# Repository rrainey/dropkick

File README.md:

# Dropkick
**An experimental logger for skydivers**

These devices are designed to be carried in a skydiver's breast pocket. The device loggs GPS position, barometric altitude, body rotation rates, and acceleration forces.
Data is logged to a SD card for analysis on the ground.

There are two board variants active in this project: V4 SAM, is the board I use for skydiving. V5-CAM is a design repurposed for real-time
use on a telescope pointing experiments. See [CHANGELOG.md](CHANGELOG.md) for a more detailed history.

## Sponsorship
I'd like to thank [PCBWay](https://www.pcbway.com/) for their generous sponsorship. PCBWay supplied prototype PCBs and solder stencils for the CAM variant of this project. My experience with PCBWay predates their sponsorship here. PCBWay has been a great choice for my projects. They deliver good PCBs and accurate stencils quickly.
 
 ## Description

This is a stand-alone, battery-powered data logger designed to be
carried by a skydiver during their jump.  It includes a GNSS (GPS) receiver, 6-DOF IMU, and altitude sensors. Data from all sensors is logged onto a Micro-SD card. The logged data can be reviewed post-jump by to-be-designed software.

One objective of this project is to research compact GNSS receiver performance in the dynamic environment that a skydiver routinely experiences. As such, there are currently two different u-blox receiver modules that I'm testing. There is a distinct PCB for each board variant.

## Directory Structure
* **pcb-sam** - KiCad 6 PCB project files for the [u-blox SAM-M10Q](https://content.u-blox.com/sites/default/files/SAM-M8Q_DataSheet_%28UBX-16012619%29.pdf) variant (this is the preferred variant for skydiving)
* **pcb-cam** - KiCad 7 PCB project files for the [u-blox CAM-M8](https://content.u-blox.com/sites/default/files/CAM-M8-FW3_DataSheet_%28UBX-15031574%29.pdf) variant
* **enclosure** - Fusion 360 enclosure; designed to be 3D-printed
* **firmware** - Arduino-based firmware for the microcontroller
* **images** - supporting images and videos
* **analysis** - GNU Octave-based log file analysis software

Gerber production files generated by KiCad are included in the PCB directories.

Exploded enclosure view (click to view)

## Specifications

Enclosure Dimensions: 58mm x 51mm x 20mm

Power: rechargeable 500mAh Li-Polymer battery

Unit Weight: 55 grams

Storage: removable microSD card

Log file format: [one log file for each jump](LOG-FORMAT.md); raw log format is an extension of NMEA0183.

USB micro-B connector (for recharging and programming)

Bootloader programmed via a 10-pin J-Link compatible connector; routine Arduino programming via the USB connector.

** Compiling Firmware
The Arduino board type should be set to "Adafruit Trinket M0" with Tiny USB enabled.

These libraries are required:
- Adafruit_BMP3XX
- ICM42688
- SparkFun u-blox GNSS Arduino_Library
- MicroNMEA  (2.0.6)
- SD (install the custom fork that I maintain on github)

## PCB Notes
My prototype circuit boards were fabricated by both OSHPark and PCBgogo. Both are excellent manufacturers for hobbyists.

### Bootloader

I flash all variants with the [Adafruit Trinket M0 UF2 bootloader](https://github.com/adafruit/uf2-samdx1/releases/download/v3.15.0/bootloader-trinket_m0-v3.15.0.bin) bin image. The current version is 3.15. Programming is performed via a Segger J-Link USB adapter using Microchip Studio (formerly Atmel Studio). Use Device = "ATSAMD21G18A". Program from the bootload .bin image file and then set the USER_WORD_0.NVMCTRL_BOOTPROT fuse to 8192 bytes.

## Solder Reflow

The solder reflow process has turned out to be a tricky step in constructing the PCBs, particularly with the SAM-M8Q IC.  Basically it requires extra heat soak in
  order to properly flow the solder.  Some u-blox instructions are repeated below, but I'll ultimately add some notes about what worked best for me.

The [u-blox Hardware Integration Manual](https://www.u-blox.com/en/docs/UBX-16018358) provides some detailed requirements for soldering the GNSS module to a PCB:

> ### Soldering paste

>Use of "no clean" soldering paste is highly recommended, as it does not require cleaning after the soldering process has taken place. The paste in the example below meets these criteria.

> * Soldering paste: OM338 SAC405 / Nr.143714 (Cookson Electronics)

> * Alloy specification: Sn 95.5/ Ag 4/ Cu 0.5 (95.5% tin/ 4% silver/ 0.5% copper)

> * Melting temperature: 217 °C

> * Stencil thickness: 120 um

> The final choice of the soldering paste depends on the approved manufacturing procedures. The paste-mask geometry for applying soldering paste should meet the recommendations. 

> ### Reflow soldering

> A convection-type soldering oven is highly recommended over the infrared-type radiation oven. Convection-heated ovens allow precise control of the temperature, and all parts will heat up evenly, regardless of material properties, thickness of components and surface color. As a reference, see the "IPC-7530 Guidelines for temperature profiling for mass soldering (reflow and wave) processes”, published in 2001.

> ### Preheat phase

>During the initial heating of component leads and balls, residual humidity will be dried out. Note that this preheat phase will not replace prior baking procedures.

> * Temperature rise rate: max. 3 °C/s. If the temperature rise is too rapid in the preheat phase it may cause excessive slumping.

> * Time: 60 - 120 s. If the preheat is insufficient, rather large solder balls tend to generate. Conversely, if performed excessively, fine balls and large balls will be generated in clusters.

> * End temperature: 150 - 200 °C. If the temperature is too low, non-melting tends to be caused in areas containing large heat capacity. 

> ### Heating and Reflow Phase

> The temperature rises above the liquidus temperature of 217 °C. Avoid a sudden rise in temperature as the slump of the paste could become worse.

> * Limit time above 217 °C liquidus temperature: 40 - 60s

> * Peak reflow temperature: 245 °C

SAC405 solder paste is relatively expensive. I have been unable to locate SAC405 in hobbyist-friendly quantities, so I opted to use SAC305 for these prototypes. The melting qualities are quite similar, and it retains the essential "no clean" properties required by U-blox -- at the cost of [potentially having slightly less sound solder connections](https://citeseerx.ist.psu.edu/viewdoc/download?doi=10.1.1.517.4830&rep=rep1&type=pdf#:~:text=The%20North%20American%20industry%20generally,comparable%20to%20that%20of%20SAC405.).

I own a very basic infrared-type reflow oven, a Puhui T962. Even though infrared ovens are not recommended by U-blox, I decided to use it and pay careful attention to the programming of heating profile. First, I did a series to timing experiments with the standard profiles comparing them against the u-blox requirements. It turned out that my oven does not have a standard heating profile that would comply with these requirements. In particular, the closest standard profile held the oven temperature above 217 °C for roughly 90 seconds. That's far longer than the 40 to 60 seconds stated in the requirements. I had to develop a custom profile to match.

I programmed this profile into the reflow oven:

## Enclosure Notes
The enclosure is designed to be 3D printed. Tolerances between the upper enclosure, lower enclosure, and the PCB
 are quite tight - printing precision will be important. Since 3D printing technologies will vary in their precision, 
 you may need to scale or otherwise modify the objects to adequately match the final measurements in the original design.

For example, I printed the prototype enclosure on a MakerBot Replicator 2 (PLA) printer.  Using the default print settings
 I know that an object will shrink typically by about 1% post-printing.  I set the scale to 101% to compensate for that 
 in the MakerBot Desktop tooling and the end result works well.

## Credits

This PCB design is based on several Adafruit Feather and Stemma QT sensor boards.  Adafruit maintains a family of
 excellent microcontroller and sensor evaluation boards and companion software.  Support them. They deserve it.

The enclosure for this project was designed using the personal edition of Fusion 360. Autodesk supports the Maker community through access to this epic design tool.  Try it out.

## Disclaimer
THE SOFTWARE IS PROVIDED "AS IS", WITHOUT WARRANTY OF ANY KIND, EXPRESS OR IMPLIED, INCLUDING BUT NOT LIMITED TO THE WARRANTIES OF MERCHANTABILITY,
FITNESS FOR A PARTICULAR PURPOSE AND NONINFRINGEMENT. IN NO EVENT SHALL THE
AUTHORS OR COPYRIGHT HOLDERS BE LIABLE FOR ANY CLAIM, DAMAGES OR OTHER
LIABILITY, WHETHER IN AN ACTION OF CONTRACT, TORT OR OTHERWISE, ARISING FROM,
OUT OF OR IN CONNECTION WITH THE SOFTWARE OR THE USE OR OTHER DEALINGS IN THE
SOFTWARE.

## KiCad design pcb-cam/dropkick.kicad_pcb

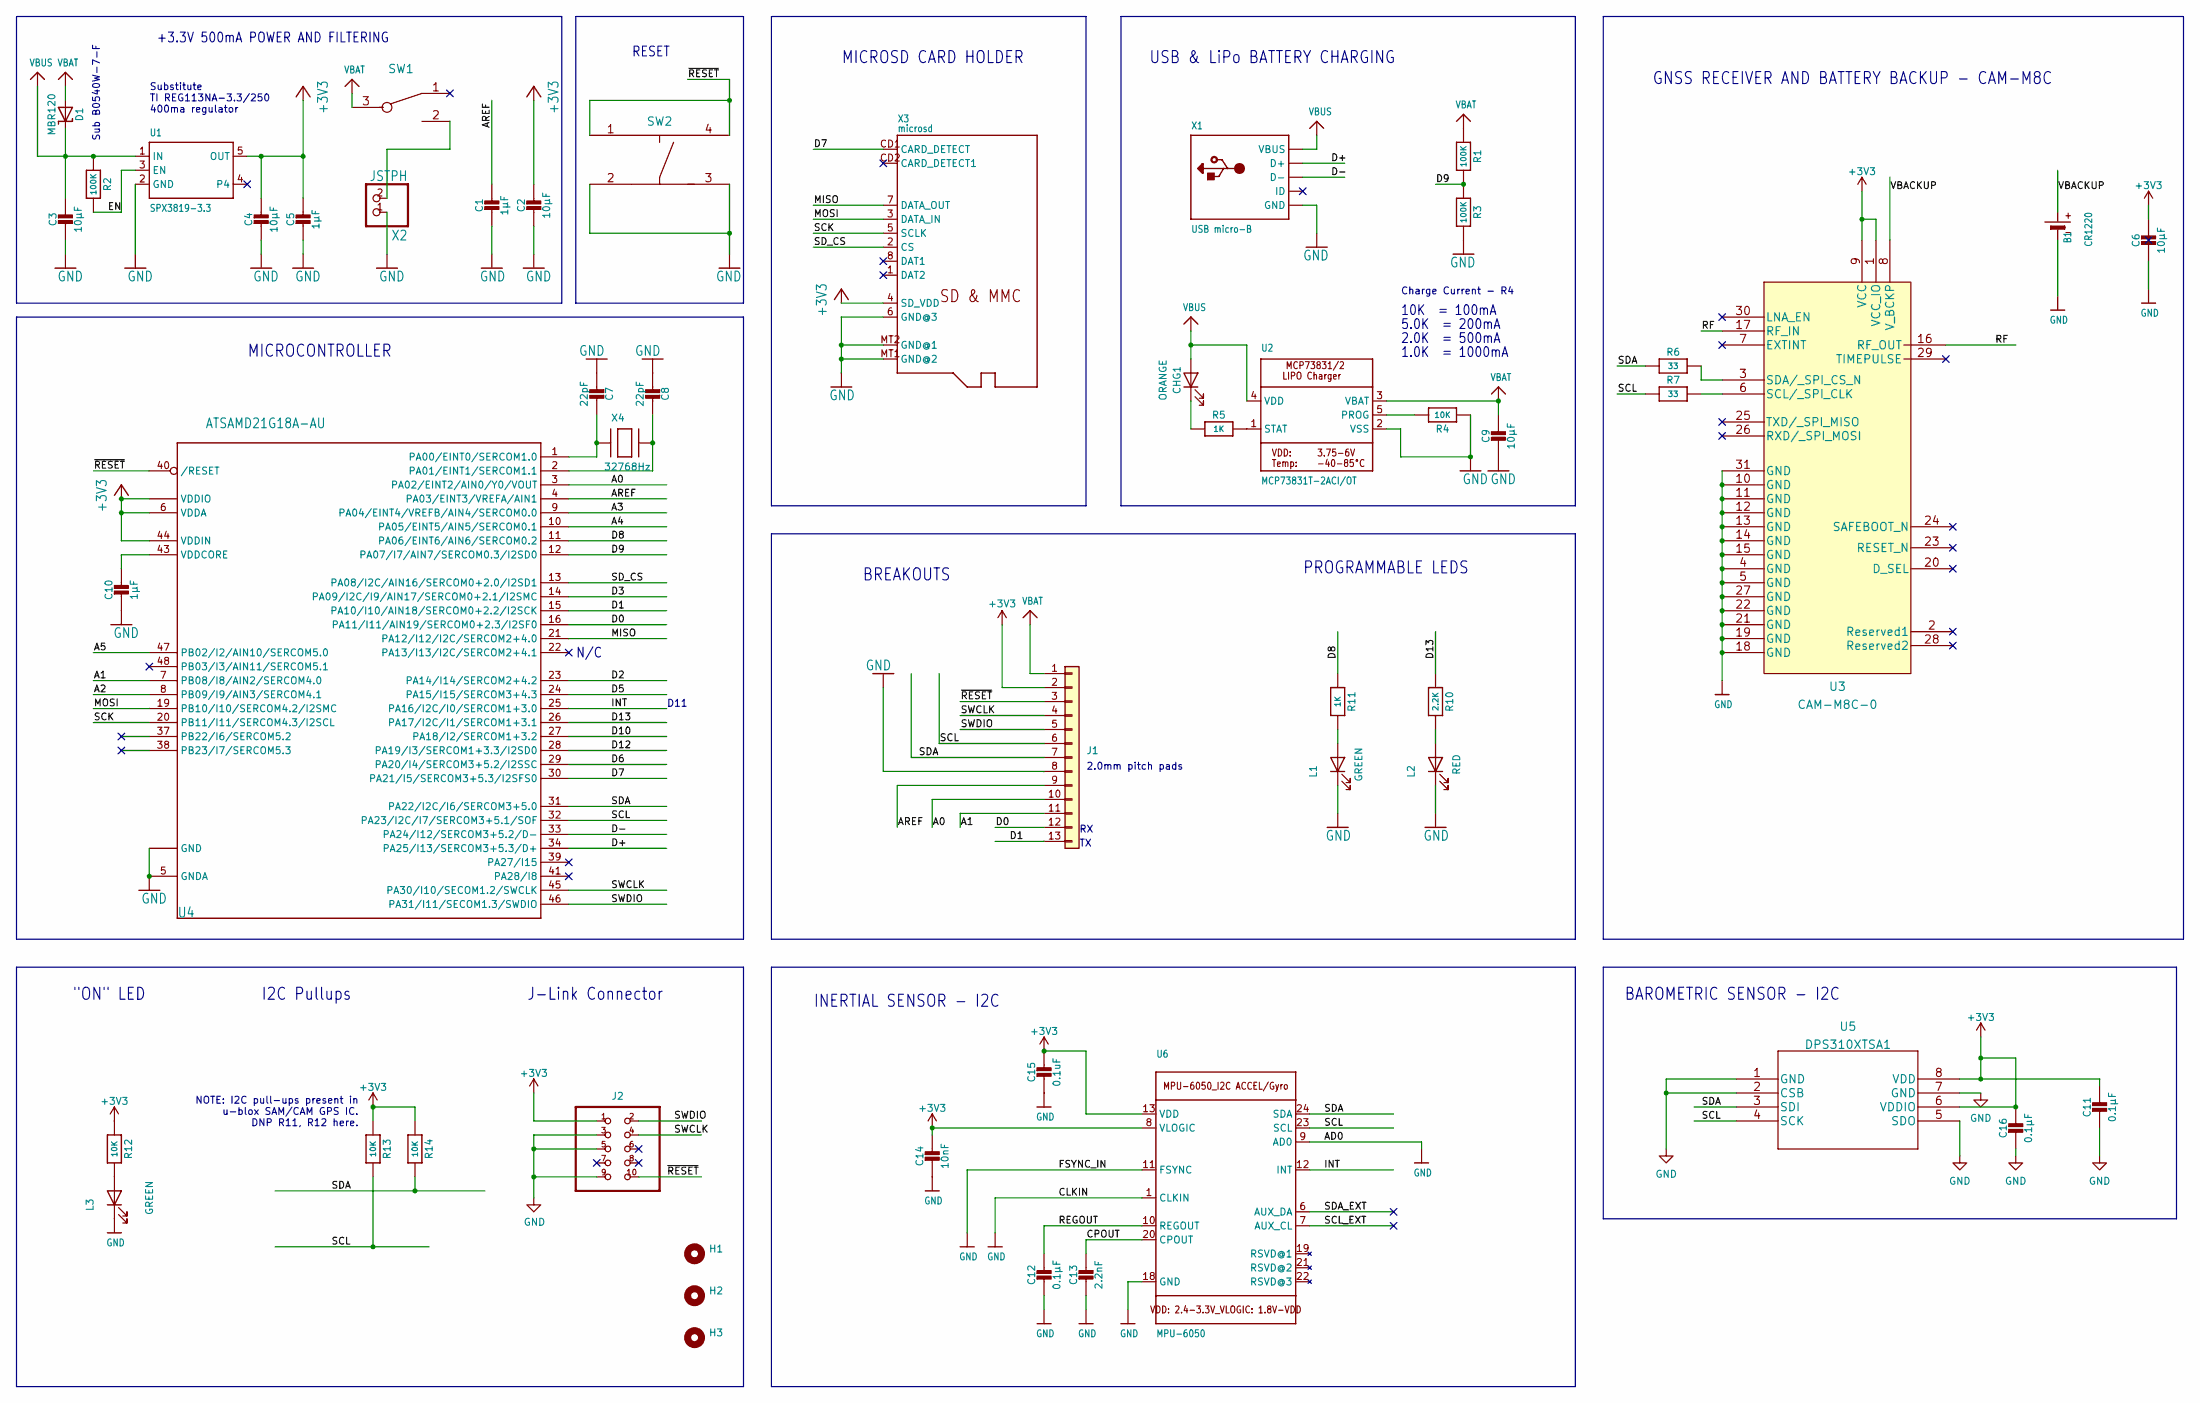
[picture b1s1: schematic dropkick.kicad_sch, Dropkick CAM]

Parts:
B1: CR1220; CR1220-2; Manufacturer Part 1056TR
C1, C5, C10: 1µF; C_0603_1608Metric
C2, C3, C4, C6, C9: 10µF; C_0805_2012Metric; Manufacturer Part C0805C106K8RACTU
C7, C8: 22pF; C_0603_1608Metric; Manufacturer Part 06035U220FAT2A
C11, C12, C16: 0.1µF; C_0603_1608Metric; Manufacturer Part VJ0603Y104JXXAC
C13: 2.2nF; C_0603_1608Metric; Manufacturer Part C0603C222K1HACAUTO
C14: 10nF; C_0603_1608Metric; Manufacturer Part C0603C222K1HACAUTO
C15: 0.1uF; C_0603_1608Metric; Manufacturer Part C0603C222K1HACAUTO
CHG1: ORANGE; LED_0603_1608Metric; Manufacturer Part AA1112H-TR
D1: MBR120; SOD-123; Manufacturer Part PMEG2005EGWX
H1, H2, H3: MountingHole; MOUNTINGHOLE_2.5_PLATED
J1: Conn_01x13; PinSocket_1x13_P2.00mm_Vertical
J2: 3221-10-0300-00-TR; Manufacturer Part 3221-10-0300-00-TR
L1, L3: GREEN; LED_0603_1608Metric; Manufacturer Part LTST-S270KGKT
L2: RED; LED_0603_1608Metric; Manufacturer Part LTST-S270KRKT
R1, R2, R3: 100K; R_0603_1608Metric; Manufacturer Part TNPW0603100KBEEA
R4, R12, R13, R14: 10K; R_0603_1608Metric
R5, R11: 1K; R_0603_1608Metric
R6, R7: 33; R_0402_1005Metric
R10: 2.2K; R_0603_1608Metric; Manufacturer Part CRCW06032K20FKEAHP
SW1: 450405020524; Manufacturer Part 450405020524
SW2: KMR211NG_LFS; KMR211NG LFS; Manufacturer Part KMR211NG LFS
U1: SPX3819-3.3; SOT23-5; Manufacturer Part SPX3819M5-L-3-3/TR
U2: MCP73831T-2ACI/OT; SOT23-5; Manufacturer Part MCP73831T-2ACI/OT
U3: CAM-M8C-0; Manufacturer Part CAM-M8C-0
U4: ATSAMD21G18A-AU; ATSAMD21G15B-AU; Manufacturer Part ATSAMD21G18A-AU
U5: DPS310XTSA1; Manufacturer Part DPS310XTSA1
U6: MPU-6050; MPU6XXX_QFN24_4MM_SMSC; Manufacturer Part MPU-6050
X1: USB micro-B; 4UCONN_20329_V2; Manufacturer Part 4UCONN_20329_V2
X2: JSTPH; JSTPH2; Manufacturer Part S2B-PH-SM4-TB
X3: microsd; MICROSD; Manufacturer Part MEM2061-01-188-00-A
X4: 32768Hz; XTAL3215; Manufacturer Part FC-135 32.7680KA-A5

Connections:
+3V3: C2.1, C4.1, C5.1, C6.1, C11.1, C14.1, C15.1, C16.1, J1.2, J2.1, R12.1, R13.1, R14.1, U1.5 (OUT), U3.1 (VCC_IO), U3.9 (VCC), U4.6 (VDDA), U4.17 (VDDIO), U4.36 (VDDIO), U4.44 (VDDIN), U5.6 (VDDIO), U5.8 (VDD), U6.8 (VLOGIC), U6.13 (VDD), X3.4 (SD_VDD)
/A0: J1.10, U4.3 (PA02/EINT2/AIN0/Y0/VOUT)
/A1: J1.11, U4.7 (PB08/I8/AIN2/SERCOM4.0)
/A2: U4.8 (PB09/I9/AIN3/SERCOM4.1)
/A3: U4.9 (PA04/EINT4/VREFB/AIN4/SERCOM0.0)
/A4: U4.10 (PA05/EINT5/AIN5/SERCOM0.1)
/A5: U4.47 (PB02/I2/AIN10/SERCOM5.0)
/AREF: C1.1, J1.9, U4.4 (PA03/EINT3/VREFA/AIN1)
/CPOUT: C13.1, U6.20 (CPOUT)
/D0: J1.12, U4.16 (PA11/I11/AIN19/SERCOM0+2.3/I2SF0)
/D1: J1.13, U4.15 (PA10/I10/AIN18/SERCOM0+2.2/I2SCK)
/D2: U4.23 (PA14/I14/SERCOM2+4.2)
/D3: U4.14 (PA09/I2C/I9/AIN17/SERCOM0+2.1/I2SMC)
/D5: U4.24 (PA15/I15/SERCOM3+4.3)
/D6: U4.29 (PA20/I4/SERCOM3+5.2/I2SSC)
/D7: U4.30 (PA21/I5/SERCOM3+5.3/I2SFS0), X3.CD1 (CARD_DETECT)
/D8: R11.1, U4.11 (PA06/EINT6/AIN6/SERCOM0.2)
/D9: R1.2, R3.1, U4.12 (PA07/I7/AIN7/SERCOM0.3/I2SD0)
/D10: U4.27 (PA18/I2/SERCOM1+3.2)
/D12: U4.28 (PA19/I3/SERCOM1+3.3/I2SD0)
/D13: R10.1, U4.26 (PA17/I2C/I1/SERCOM1+3.1)
/D+: U4.34 (PA25/I13/SERCOM3+5.3/D+), X1.D+
/D-: U4.33 (PA24/I12/SERCOM3+5.2/D-), X1.D-
/EN: R2.2, U1.3 (EN)
/INT: U4.25 (PA16/I2C/I0/SERCOM1+3.0), U6.12 (INT)
/MISO: U4.21 (PA12/I12/I2C/SERCOM2+4.0), X3.7 (DATA_OUT)
/MOSI: U4.19 (PB10/I10/SERCOM4.2/I2SMC), X3.3 (DATA_IN)
/REGOUT: C12.1, U6.10 (REGOUT)
/RF: U3.16 (RF_OUT), U3.17 (RF_IN)
/SCK: U4.20 (PB11/I11/SERCOM4.3/I2SCL), X3.5 (SCLK)
/SCL: J1.6, R7.1, R13.2, U4.32 (PA23/I2C/I7/SERCOM3+5.1/SOF), U5.4 (SCK), U6.23 (SCL)
/SCL_EXT: U6.7 (AUX_CL)
/SDA: J1.7, R6.1, R14.2, U4.31 (PA22/I2C/I6/SERCOM3+5.0), U5.3 (SDI), U6.24 (SDA)
/SDA_EXT: U6.6 (AUX_DA)
/SD_CS: U4.13 (PA08/I2C/AIN16/SERCOM0+2.0/I2SD1), X3.2 (CS)
/SWCLK: J1.4, J2.4, U4.45 (PA30/I10/SECOM1.2/SWCLK)
/SWDIO: J1.5, J2.2, U4.46 (PA31/I11/SECOM1.3/SWDIO)
/VBACKUP: B1.+, U3.8 (V_BCKP)
/~RESET: J1.3, J2.10, SW2.1, SW2.4, U4.40 (/RESET)
GND: B1.-, C1.2, C2.2, C3.2, C4.2, C5.2, C6.2, C7.2, C8.2, C9.2, C10.2, C11.2, C12.2, C13.2, C14.2, C15.2, C16.2, J1.8, J2.3, J2.5, J2.9, L1.1 (K), L2.1 (K), L3.1 (K), R3.2, R4.2, SW2.2, SW2.3, U1.2 (GND), U2.2 (VSS), U3.4 (GND), U3.5 (GND), U3.10 (GND), U3.11 (GND), U3.12 (GND), U3.13 (GND), U3.14 (GND), U3.15 (GND), U3.18 (GND), U3.19 (GND), U3.21 (GND), U3.22 (GND), U3.27 (GND), U3.31 (GND), U4.5 (GNDA), U4.18 (GND), U4.35 (GND), U4.42 (GND), U5.1 (GND), U5.2 (CSB), U5.5 (SDO), U5.7 (GND), U6.1 (CLKIN), U6.9 (AD0), U6.11 (FSYNC), U6.18 (GND), X1.BASE@1 (GND), X1.BASE@2 (GND), X1.GND, X1.SPRT@1 (GND), X1.SPRT@2 (GND), X1.SPRT@3 (GND), X1.SPRT@4 (GND), X2.1, X3.6 (GND@3), X3.MT1 (GND@2), X3.MT2 (GND@1)
unnamed: CHG1.1 (K), R5.1
unnamed: L1.2 (A), R11.2
unnamed: L2.2 (A), R10.2
unnamed: L3.2 (A), R12.2
unnamed: SW1.2, X2.2
unnamed: R4.1, U2.5 (PROG)
unnamed: R5.2, U2.1 (STAT)
unnamed: R7.2, U3.6 (SCL/_SPI_CLK)
unnamed: R6.2, U3.3 (SDA/_SPI_CS_N)
unnamed: C7.1, U4.1 (PA00/EINT0/SERCOM1.0), X4.P$1
unnamed: C8.1, U4.2 (PA01/EINT1/SERCOM1.1), X4.P$2
unnamed: C10.1, U4.43 (VDDCORE)
VBAT: C9.1, D1.A, J1.1, R1.1, SW1.3, U2.3 (VBAT)
VBUS: C3.1, CHG1.2 (A), D1.C, R2.1, U1.1 (IN), U2.4 (VDD), X1.VBUS

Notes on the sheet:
BAROMETRIC SENSOR - I2C
GNSS RECEIVER AND BATTERY BACKUP - CAM-M8C
"ON" LED
N/C
I2C Pullups
10K = 100mA
INERTIAL SENSOR - I2C
MICROCONTROLLER
1.0K = 1000mA
Charge Current - R4
5.0K = 200mA
BREAKOUTS
RESET
D11
+3.3V 500mA POWER AND FILTERING
J-Link Connector
Substitute TI REG113NA-3.3/250 400ma regulator
PROGRAMMABLE LEDS
2.0mm pitch pads
2.0K = 500mA
MICROSD CARD HOLDER
USB & LiPo BATTERY CHARGING
NOTE: I2C pull-ups present in u-blox SAM/CAM GPS IC. DNP R11, R12 here.
Sub B0540W-7-F

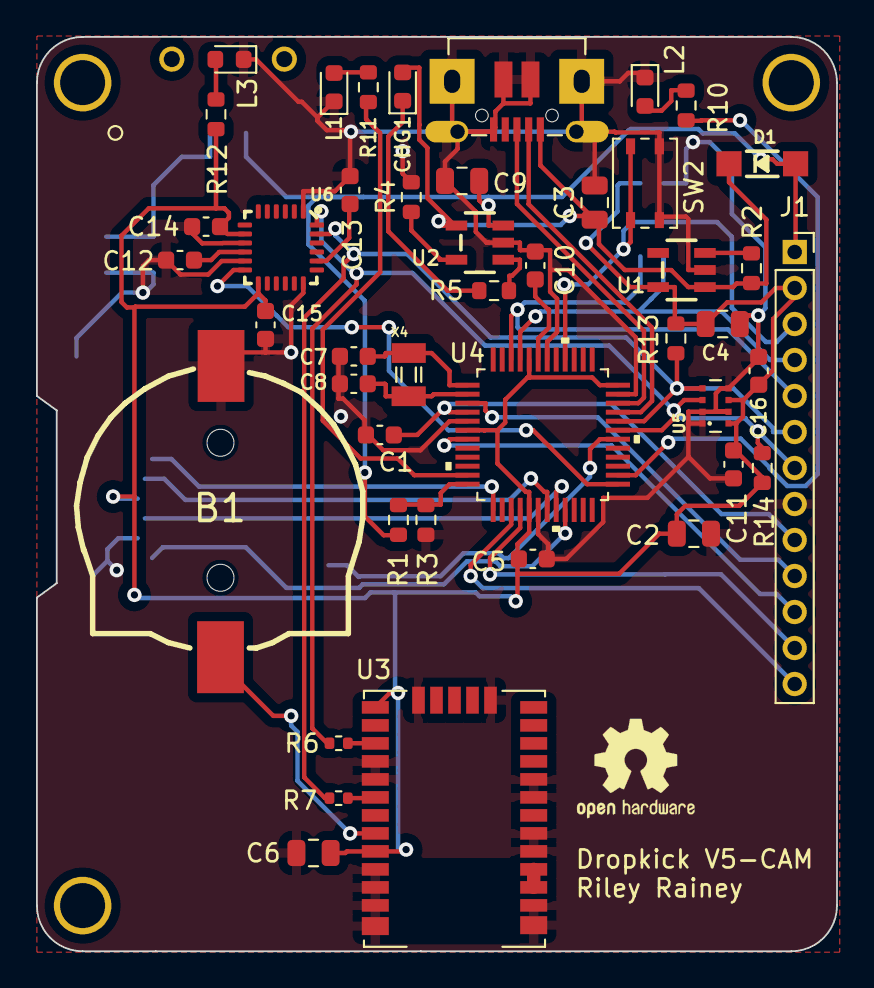
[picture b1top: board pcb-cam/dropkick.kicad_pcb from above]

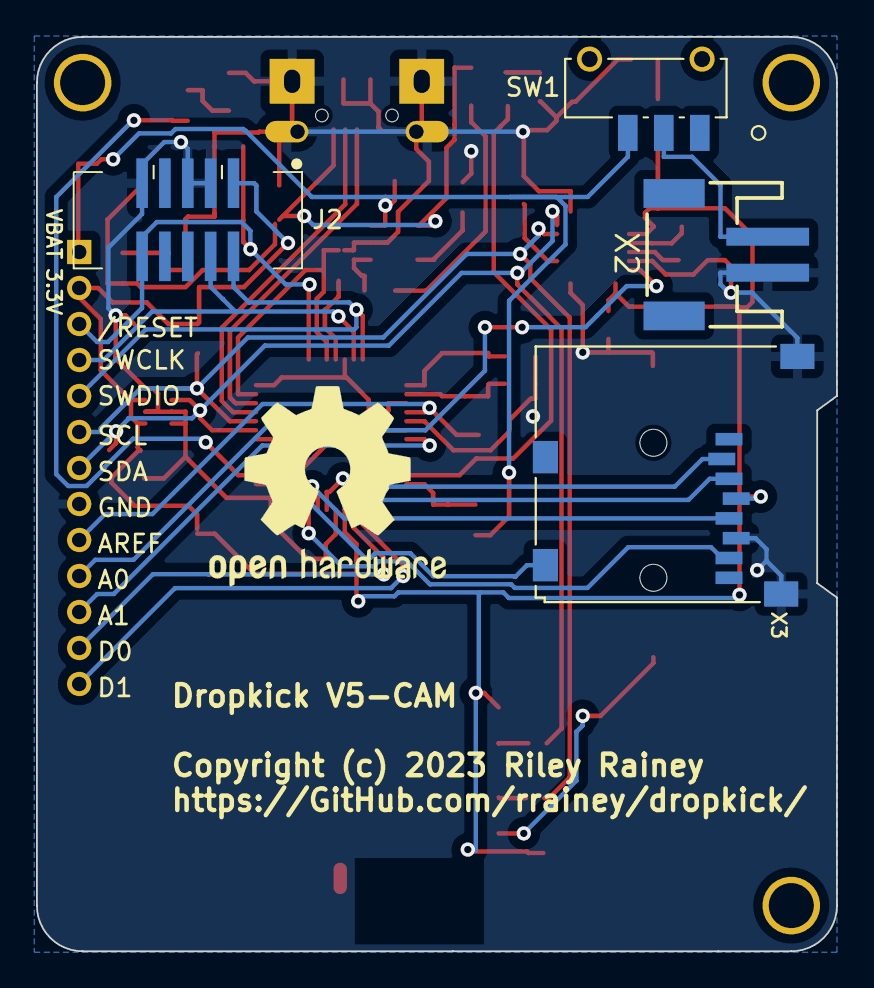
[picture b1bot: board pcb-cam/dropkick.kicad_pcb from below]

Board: 2 copper layers, 44.5 x 50.8 mm, 53 parts (5 on the bottom side), 42 nets.

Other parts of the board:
REF1: OSHW-Logo2_7.3x6mm_SilkScreen
REF2: OSHW-Logo2_14.6x12mm_SilkScreen

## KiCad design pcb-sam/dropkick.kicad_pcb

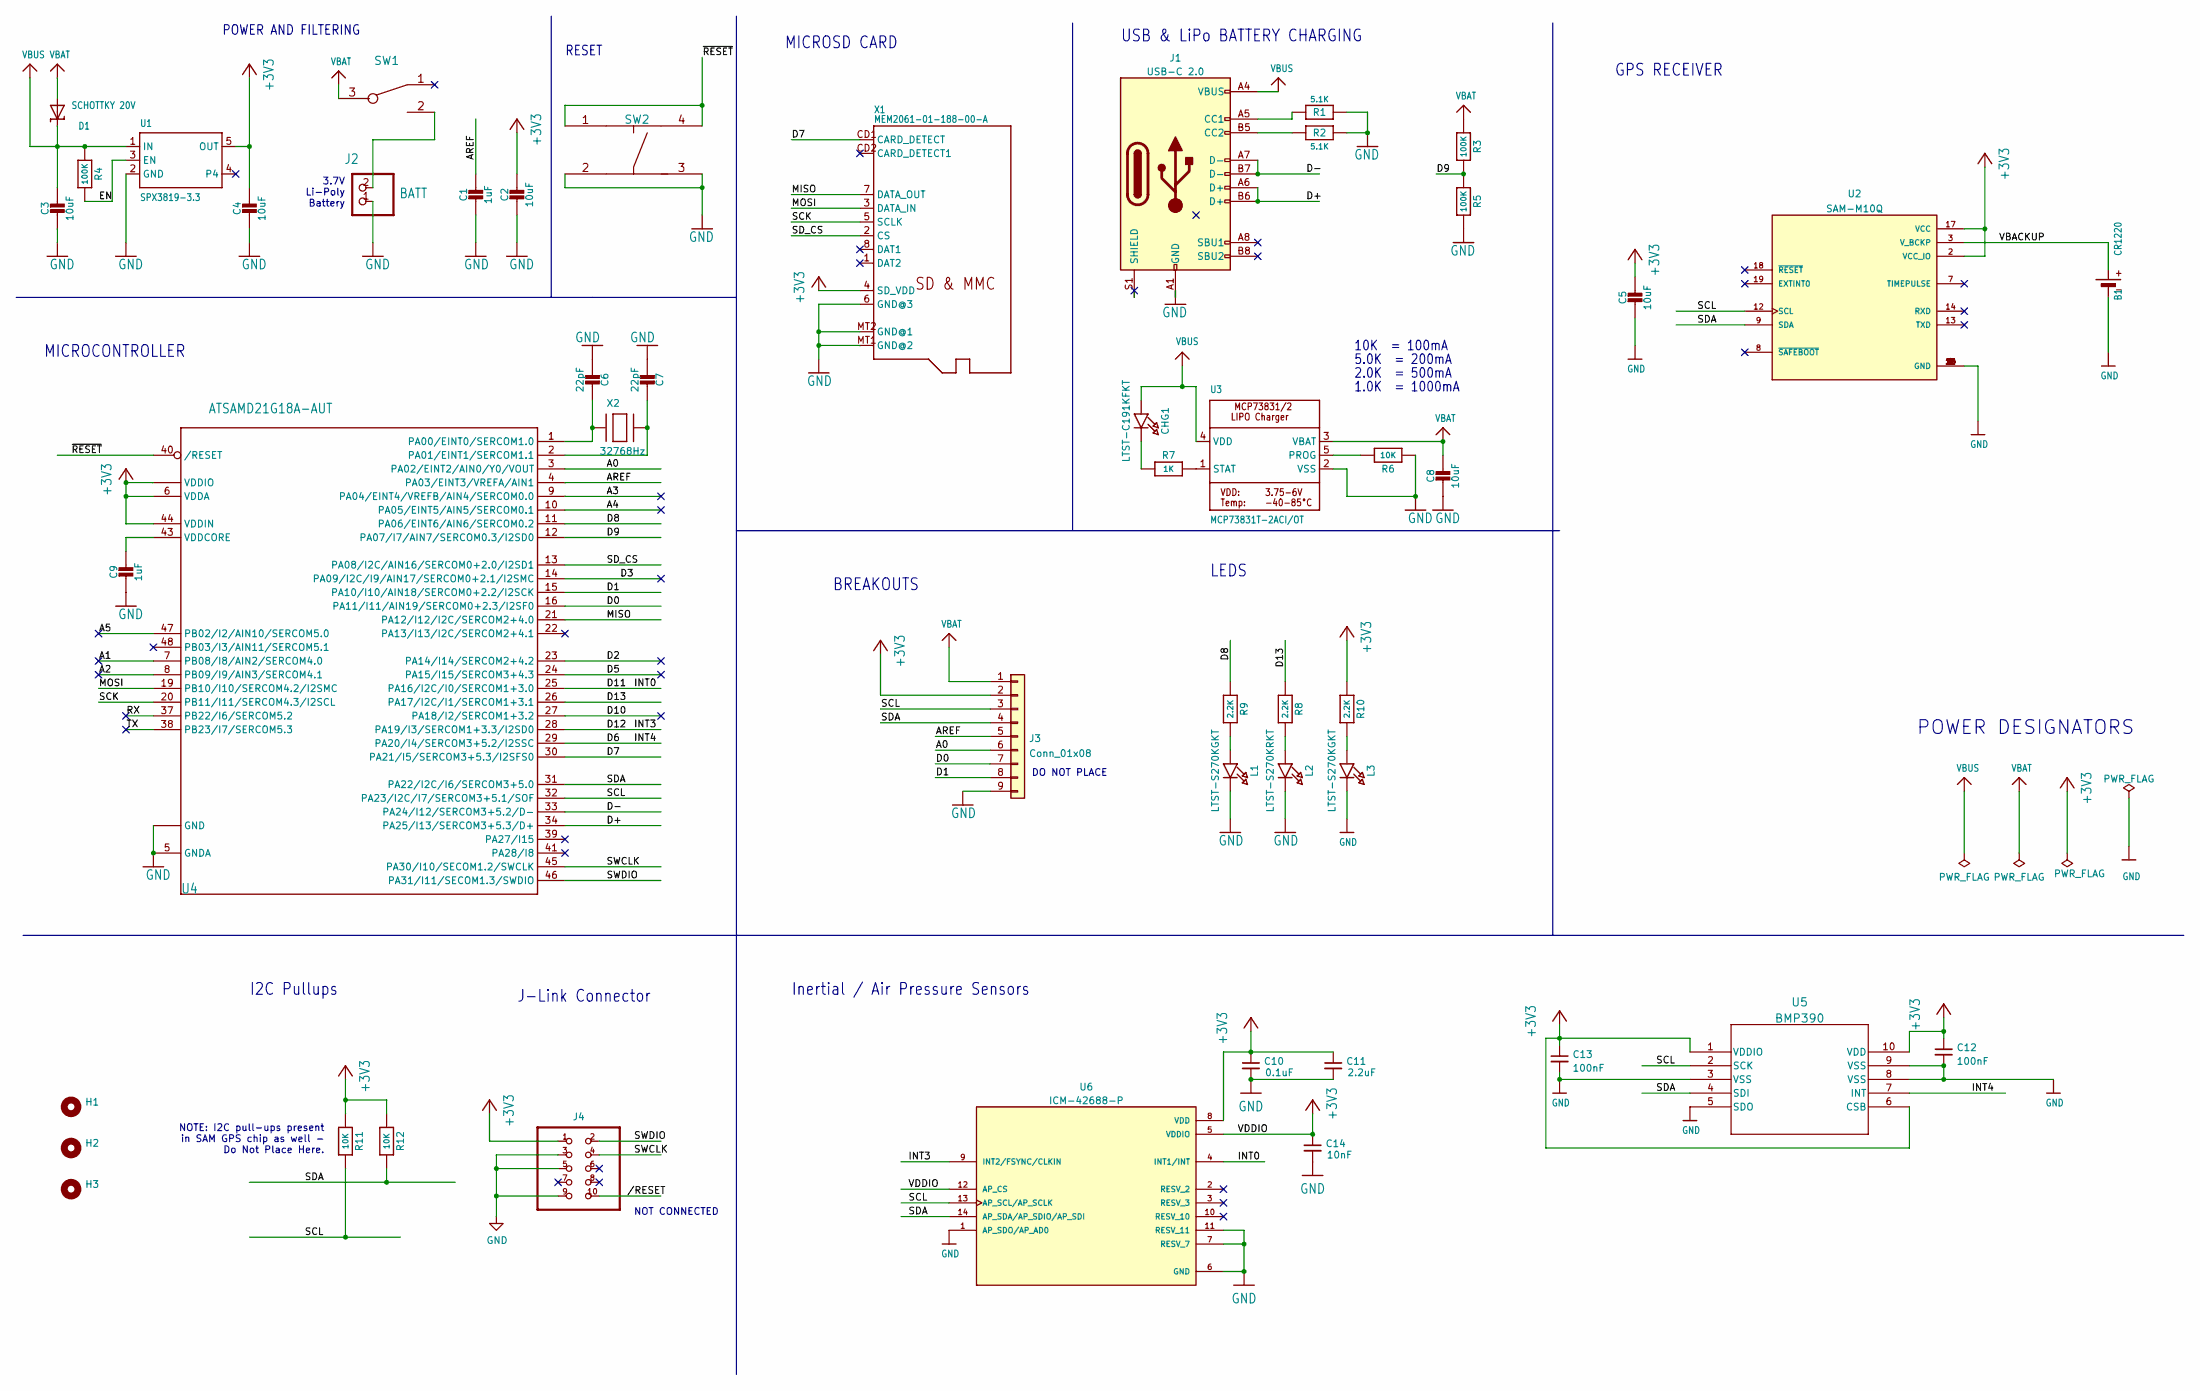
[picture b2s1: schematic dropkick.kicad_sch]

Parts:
B1: CR1220; CR1220-2; MPN 1056TR
C1, C9: 1uF; C_0603_1608Metric
C2, C3, C4, C5, C8: 10uF; C_0805_2012Metric
C6, C7: 22pF; C_0603_1608Metric
C10: 0.1uF; C_0603_1608Metric
C11: 2.2uF; C_0603_1608Metric
C12, C13: 100nF; C_0603_1608Metric
C14: 10nF; C_0603_1608Metric
CHG1: LTST-C191KFKT; CHIPLED_0603_NOOUTLINE; MPN LTST-C191KFKT
D1: SCHOTTKY 20V; D_SOD-123F; MPN SM5817PL-TP
H1, H2, H3: MountingHole; MOUNTINGHOLE_2.5_PLATED
J1: USB-C 2.0; USB_C_Receptacle_GCT_USB4085; MPN USB4085-GF-A
J2: BATT; JSTPH2; MPN S2B-PH-SM4-TB
J3: Conn_01x08; PinHeader_1x09_P2.54mm_Vertical; MPN DNP
J4: 3221-10-0300-00-TR; MPN 3221-10-0300-00-TR
L1, L3: LTST-S270KGKT; CHIPLED_0603_NOOUTLINE; MPN LTST-S270KGKT
L2: LTST-S270KRKT; CHIPLED_0603_NOOUTLINE; MPN LTST-S270KRKT
R1, R2: 5.1K; R_0402_1005Metric
R3, R4, R5: 100K; R_0603_1608Metric
R6, R11, R12: 10K; R_0603_1608Metric
R7: 1K; R_0603_1608Metric
R8, R9, R10: 2.2K; R_0603_1608Metric
SW1: 450405020524; MPN 450405020524
SW2: KMR211NG_LFS; KMR211NG LFS; MPN KMR211NG_LFS
U1: SPX3819-3.3; SOT23-5; MPN SPX3819-3.3
U2: SAM-M10Q; MODULE_SAM-M8Q-0-10; PARTREV R07
U3: MCP73831T-2ACI/OT; SOT23-5; MPN MCP73831T-2ACI/OT
U4: ATSAMD21G18A-AUT; ATSAMD21G15B-AU; MPN ATSAMD21G18A-AUT
U5: BMP390; LGA10_BMP390_BOS
U6: ICM-42688-P; PQFN50P300X250X97-14N; PARTREV 1.2
X1: MEM2061-01-188-00-A; MICROSD; MPN MEM2061-01-188-00-A
X2: 32768Hz; XTAL3215; MPN FC-135 32.7680KA-A5

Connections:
+3V3: C2.1, C4.1, C5.1, C10.1, C11.1, C12.1, C13.1, C14.1, J3.2, J4.1, R10.1, R11.1, R12.1, U1.5 (OUT), U2.2 (VCC_IO), U2.17 (VCC), U4.6 (VDDA), U4.17 (VDDIO), U4.36 (VDDIO), U4.44 (VDDIN), U5.1 (VDDIO), U5.6 (CSB), U5.10 (VDD), U6.5 (VDDIO), U6.8 (VDD), U6.12 (AP_CS), X1.4 (SD_VDD)
/A0: J3.6, U4.3 (PA02/EINT2/AIN0/Y0/VOUT)
/A1: U4.7 (PB08/I8/AIN2/SERCOM4.0)
/A2: U4.8 (PB09/I9/AIN3/SERCOM4.1)
/A3: U4.9 (PA04/EINT4/VREFB/AIN4/SERCOM0.0)
/A4: U4.10 (PA05/EINT5/AIN5/SERCOM0.1)
/A5: U4.47 (PB02/I2/AIN10/SERCOM5.0)
/AREF: C1.1, J3.5, U4.4 (PA03/EINT3/VREFA/AIN1)
/D0: J3.7, U4.16 (PA11/I11/AIN19/SERCOM0+2.3/I2SF0)
/D1: J3.8, U4.15 (PA10/I10/AIN18/SERCOM0+2.2/I2SCK)
/D2: U4.23 (PA14/I14/SERCOM2+4.2)
/D3: U4.14 (PA09/I2C/I9/AIN17/SERCOM0+2.1/I2SMC)
/D5: U4.24 (PA15/I15/SERCOM3+4.3)
/D6: U4.29 (PA20/I4/SERCOM3+5.2/I2SSC), U5.7 (INT)
/D7: U4.30 (PA21/I5/SERCOM3+5.3/I2SFS0), X1.CD1 (CARD_DETECT)
/D8: R9.1, U4.11 (PA06/EINT6/AIN6/SERCOM0.2)
/D9: R3.2, R5.1, U4.12 (PA07/I7/AIN7/SERCOM0.3/I2SD0)
/D10: U4.27 (PA18/I2/SERCOM1+3.2)
/D11: U4.25 (PA16/I2C/I0/SERCOM1+3.0), U6.4 (INT1/INT)
/D12: U4.28 (PA19/I3/SERCOM1+3.3/I2SD0), U6.9 (INT2/FSYNC/CLKIN)
/D13: R8.1, U4.26 (PA17/I2C/I1/SERCOM1+3.1)
/D+: J1.A6 (D+), J1.B6 (D+), U4.34 (PA25/I13/SERCOM3+5.3/D+)
/D-: J1.A7 (D-), J1.B7 (D-), U4.33 (PA24/I12/SERCOM3+5.2/D-)
/EN: R4.2, U1.3 (EN)
/MISO: U4.21 (PA12/I12/I2C/SERCOM2+4.0), X1.7 (DATA_OUT)
/MOSI: U4.19 (PB10/I10/SERCOM4.2/I2SMC), X1.3 (DATA_IN)
/RX: U4.37 (PB22/I6/SERCOM5.2)
/SCK: U4.20 (PB11/I11/SERCOM4.3/I2SCL), X1.5 (SCLK)
/SCL: J3.3, R11.2, U2.12 (SCL), U4.32 (PA23/I2C/I7/SERCOM3+5.1/SOF), U5.2 (SCK), U6.13 (AP_SCL/AP_SCLK)
/SDA: J3.4, R12.2, U2.9 (SDA), U4.31 (PA22/I2C/I6/SERCOM3+5.0), U5.4 (SDI), U6.14 (AP_SDA/AP_SDIO/AP_SDI)
/SD_CS: U4.13 (PA08/I2C/AIN16/SERCOM0+2.0/I2SD1), X1.2 (CS)
/SWCLK: J4.4, U4.45 (PA30/I10/SECOM1.2/SWCLK)
/SWDIO: J4.2, U4.46 (PA31/I11/SECOM1.3/SWDIO)
/TX: U4.38 (PB23/I7/SERCOM5.3)
/VBACKUP: B1.+, U2.3 (V_BCKP)
//RESET: J4.10
/~RESET: SW2.1, SW2.4, U4.40 (/RESET)
GND: B1.-, C1.2, C2.2, C3.2, C4.2, C5.2, C6.2, C7.2, C8.2, C9.2, C10.2, C11.2, C12.2, C13.2, C14.2, J1.A1 (GND), J1.A12 (GND), J1.B1 (GND), J1.B12 (GND), J2.1, J3.9, J4.3, J4.5, J4.9, L1.C, L2.C, L3.C, R1.2, R2.2, R5.2, R6.2, SW2.2, SW2.3, U1.2 (GND), U2.1 (GND), U2.4 (GND), U2.5 (GND), U2.6 (GND), U2.10 (GND), U2.11 (GND), U2.15 (GND), U2.16 (GND), U2.20 (GND), U3.2 (VSS), U4.5 (GNDA), U4.18 (GND), U4.35 (GND), U4.42 (GND), U5.3 (VSS), U5.5 (SDO), U5.8 (VSS), U5.9 (VSS), U6.1 (AP_SDO/AP_AD0), U6.6 (GND), U6.7 (RESV_7), U6.11 (RESV_11), X1.6 (GND@3), X1.MT1 (GND@2), X1.MT2 (GND@1)
unnamed: C6.1, U4.1 (PA00/EINT0/SERCOM1.0), X2.P$1
unnamed: C7.1, U4.2 (PA01/EINT1/SERCOM1.1), X2.P$2
unnamed: C9.1, U4.43 (VDDCORE)
unnamed: CHG1.C, R7.1
unnamed: J1.A5 (CC1), R1.1
unnamed: J1.B5 (CC2), R2.1
unnamed: J2.2, SW1.2
unnamed: L1.A, R9.2
unnamed: L2.A, R8.2
unnamed: L3.A, R10.2
unnamed: R6.1, U3.5 (PROG)
unnamed: R7.2, U3.1 (STAT)
VBAT: C8.1, D1.2, J3.1, R3.1, SW1.3, U3.3 (VBAT)
VBUS: C3.1, CHG1.A, D1.1, J1.A4 (VBUS), J1.A9 (VBUS), J1.B4 (VBUS), J1.B9 (VBUS), R4.1, U1.1 (IN), U3.4 (VDD)

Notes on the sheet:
GPS RECEIVER
POWER DESIGNATORS
NOT CONNECTED
I2C Pullups
10K = 100mA
Inertial / Air Pressure Sensors
MICROCONTROLLER
1.0K = 1000mA
5.0K = 200mA
BREAKOUTS
RESET
POWER AND FILTERING
J-Link Connector
DO NOT PLACE
LEDS
3.7V Li-Poly Battery
2.0K = 500mA
MICROSD CARD
USB & LiPo BATTERY CHARGING
NOTE: I2C pull-ups present in SAM GPS chip as well - Do Not Place Here.

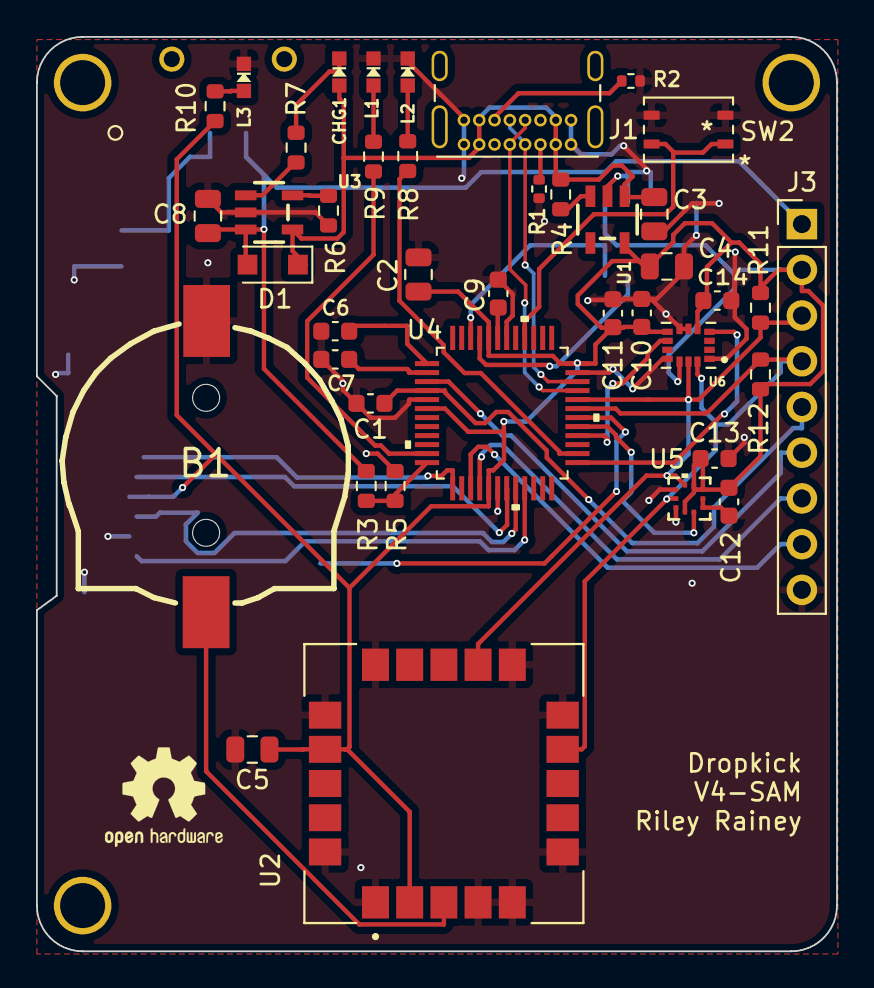
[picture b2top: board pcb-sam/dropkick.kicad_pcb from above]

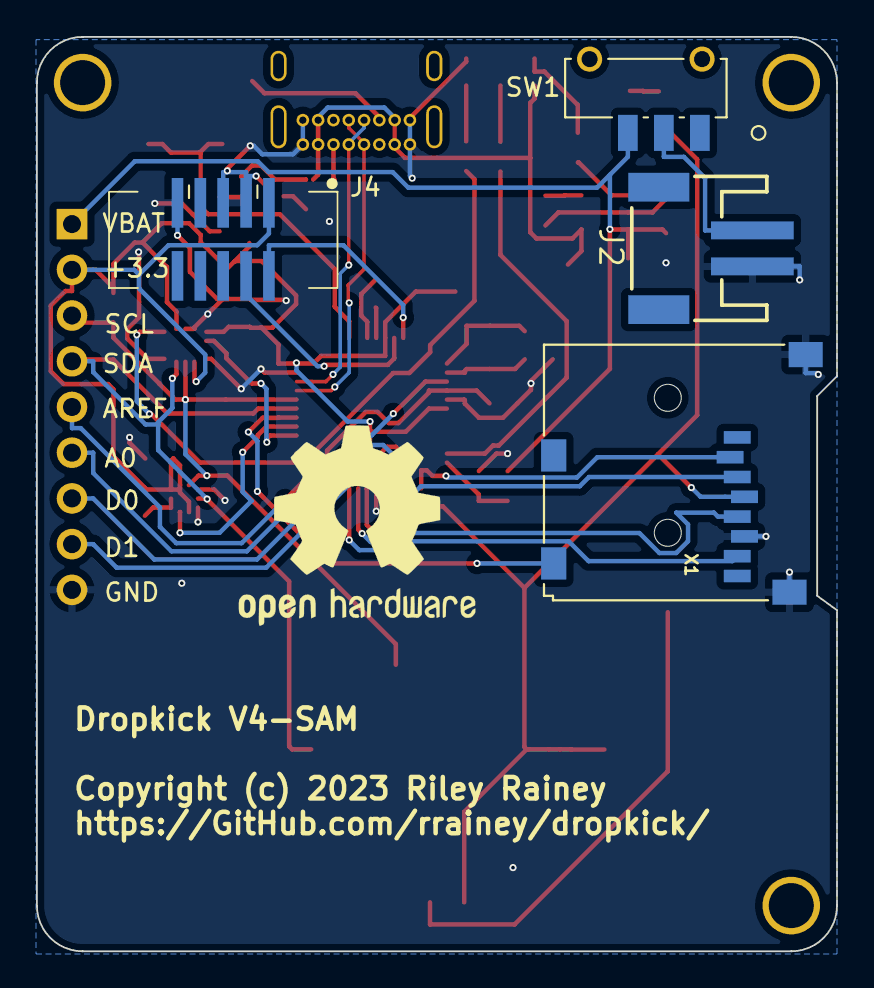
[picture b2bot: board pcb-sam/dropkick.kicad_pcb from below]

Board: 2 copper layers, 44.5 x 50.8 mm, 50 parts (5 on the bottom side), 40 nets.

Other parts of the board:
REF1: OSHW-Logo2_14.6x12mm_SilkScreen
REF2: OSHW-Logo2_7.3x6mm_SilkScreen

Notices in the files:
pcb-cam/dropkick.kicad_pcb:
Copyright (c) 2023 Riley Rainey
pcb/dropkick.kicad_pcb:
Copyright (c) 2022 Riley Rainey
parts and their libraries:
Copyright 2021 Accelerated Designs. All rights reserved.
